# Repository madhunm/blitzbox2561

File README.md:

# blitzbox2561
mini-sized ECU for speeduino firmware (5x5 cm)

2 injectors<br/>
2 active ignition coils or 1 passive ignition coil with separate ground plane<br/>
1 crankshaft sensor with VR-conditioner<br/>
6 analog inputs: CLT, IAT, TPS, BAT, Wideband Lambda, onboard MAP (4250 or 6400)<br/>

1 fuel pump out<br/>

1 idle valve out<br/>
1 tacho out<br/>
4 free and non-wired general purpose I/O's<br/>
USB programming interface with PL2303SA (Tunerstudio)<br/>

all in/outputs can be programmed different

[Link to the original speeduino project](https://www.speeduino.com "speeduino homepage")

<p align="center">
  
  <br/>

</p>

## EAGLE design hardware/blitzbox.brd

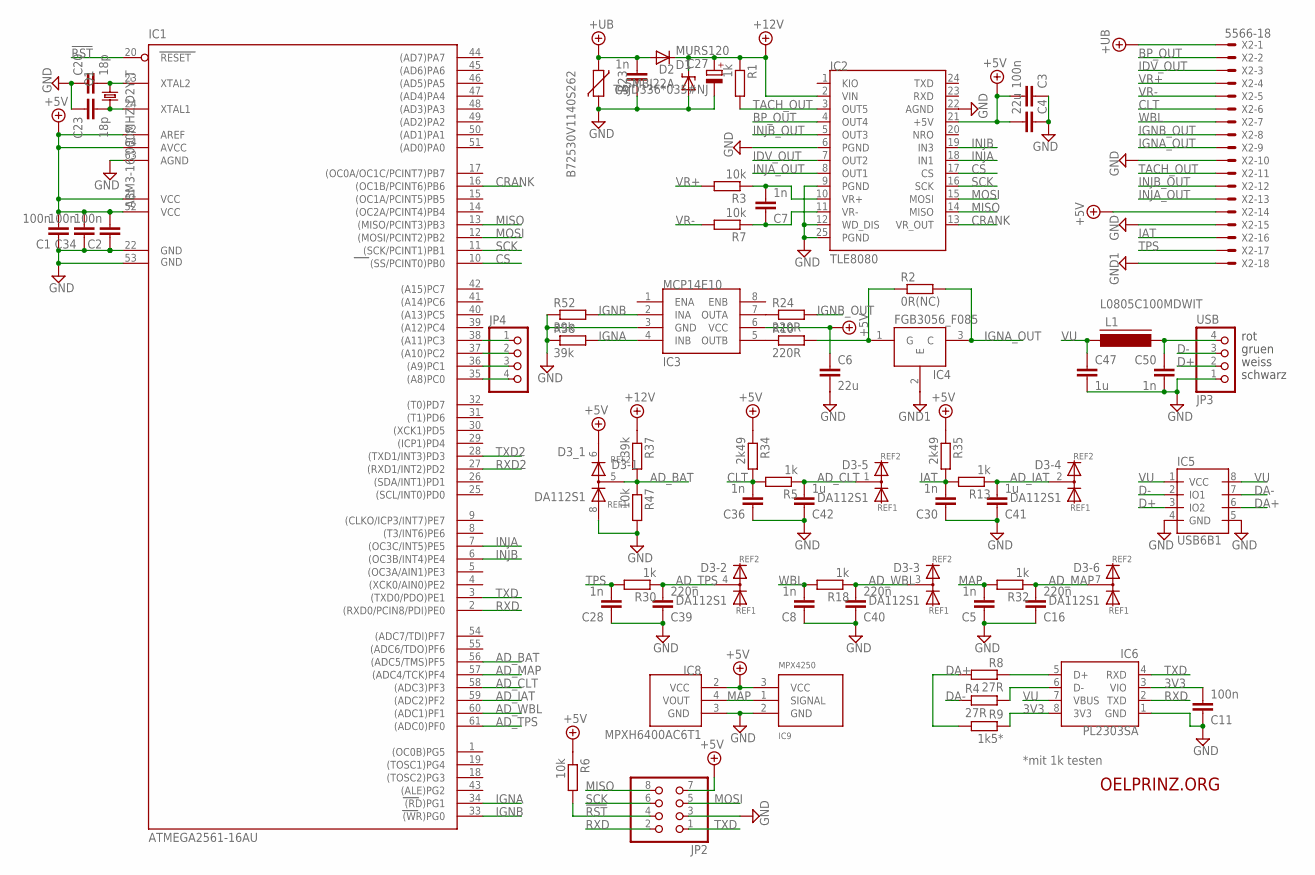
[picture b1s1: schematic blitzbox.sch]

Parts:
C1, C2, C3, C11, C34: 100n; C0805
C4: 22u; C1210
C5, C7, C8, C9, C28, C30, C36, C50: 1n; C0805
C6: 22u; C1206
C16, C39, C40: 220n; C0805
C20, C23: 18p; C0805
C27: TAJD336*035#NJ; SMC_D
C41, C42, C47: 1u; C0805
D1: MURS120
D2: SMBJ22A; SMBJ
D3: DA112S1; SO08
IC1: ATMEGA2561-16AU; TQFP64
IC2: TLE8080
IC3: MCP14E10; SO-08
IC4: FGB3056_F085; TO263
IC5: USB6B1; SO08
IC6: PL2303SA; SO-08
IC8: MPXH6400AC6T1; MPXH6400
IC9: MPX4250
JP2: PINHD-2X4; 2X04
JP3: USB; 1X04
JP4: PINHD-1X4; 1X04
L1: L0805C100MDWIT; FB805
Q1: ABM3-16.000MHZ-D2Y-T; ABM3
R1, R5, R13, R18, R30, R32: 1k; R0805
R2: 0R(NC); R0805
R3, R6, R7, R47: 10k; R0805
R4, R8: 27R; R0805
R9: 1k5*; R0805
R10, R24: 220R; R0805
R23: B72530V1140S262; CT/CN1210
R34, R35: 2k49; R0805
R37, R52, R58: 39k; R0805
X2: 5566-18

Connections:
3V3: C11.2, IC6.3 (VIO), IC6.8 (3V3), R9.1
!RST: IC1.20 (RESET), JP2.4, R6.2
+5V: C1.2, C2.2, C3.2, C4.2, C6.1, C34.2, D3.6 (REF2), IC1.21 (VCC), IC1.52 (VCC1), IC1.62 (AREF), IC1.64 (AVCC), IC2.21 (+5V), IC3.6 (VCC), IC8.2 (VCC), IC9.3 (VCC), JP2.7, R6.1, R34.1, R35.1, X2.14
+5VU: C50.1, JP3.4, L1.2
+12V: C27.+, D1.2 (C), D2.C, IC2.2 (VIN), R1.1, R37.1
+UB: C9.2, D1.1 (A), R23.2, X2.1
AD_BAT: D3.5 (K), IC1.56 ((ADC5/TMS)PF5), R37.2, R47.1
AD_CLT: C42.2, D3.1 (K), IC1.58 ((ADC3)PF3), R5.1
AD_IAT: C41.2, D3.2 (K), IC1.59 ((ADC2)PF2), R13.1
AD_MAP: C16.2, D3.7 (K), IC1.57 ((ADC4/TCK)PF4), R32.1
AD_TPS: C39.2, D3.4 (K), IC1.61 ((ADC0)PF0), R30.1
AD_WBL: C40.2, D3.3 (K), IC1.60 ((ADC1)PF1), R18.1
BP_OUT: IC2.4 (OUT4), X2.2
CLT: C36.2, R5.2, R34.2, X2.6
CRANK: IC1.16 ((OC1B/PCINT6)PB6), IC2.13 (VR_OUT)
CS: IC1.10 ((SS/PCINT0)PB0), IC2.17 (CS)
D+: IC5.3 (IO2), JP3.2
D-: IC5.2 (IO1), JP3.3
DA+: IC5.6 (IO2), R8.2, R9.2
DA-: IC5.7 (IO1), R4.1
GND: C1.1, C2.1, C3.1, C4.1, C5.1, C6.2, C8.1, C9.1, C11.1, C16.1, C20.1, C23.1, C27.-, C28.1, C30.1, C34.1, C36.1, C39.1, C40.1, C41.1, C42.1, C47.2, C50.2, D2.A, D3.8 (REF1), IC1.22 (GND), IC1.53 (GND1), IC1.63 (AGND), IC2.6 (PGND), IC2.9 (PGND), IC2.12 (WD_DIS), IC2.22 (AGND), IC2.25 (PGND), IC3.3 (GND), IC5.4 (GND), IC5.5 (GND), IC6.1 (GND), IC8.3 (GND), IC9.2 (GND), JP2.3, JP3.1, R23.1, R47.2, R52.1, R58.1, X2.10, X2.15
GND1: IC4.2 (E), X2.18
IAT: C30.2, R13.2, R35.2, X2.16
IDV_OUT: IC2.7 (OUT2), X2.3
IGN: IC4.1 (G), R2.1, R10.2
IGNA: IC1.34 ((RD)PG1), IC3.4 (INB), R58.2
IGNA_OUT: IC4.3 (C), R2.2, X2.9
IGNB: IC1.33 ((WR)PG0), IC3.2 (INA), R52.2
IGNB_OUT: R24.2, X2.8
INJA: IC1.7 ((OC3C/INT5)PE5), IC2.18 (IN1)
INJA_OUT: IC2.8 (OUT1), X2.13
INJB: IC1.6 ((OC3B/INT4)PE4), IC2.19 (IN3)
INJB_OUT: IC2.5 (OUT3), X2.12
MAP: C5.2, IC8.4 (VOUT), IC9.1 (SIGNAL), R32.2
MISO: IC1.13 ((MISO/PCINT3)PB3), IC2.14 (MISO), JP2.8
MOSI: IC1.12 ((MOSI/PCINT2)PB2), IC2.15 (MOSI), JP2.5
unnamed: C7.1, IC2.11 (VR-), R7.1
unnamed: IC3.5 (OUTB), R10.1
unnamed: IC6.6 (D-), R4.2
unnamed: IC6.5 (D+), R8.1
unnamed: IC1.38 ((A11)PC3), JP4.1
unnamed: IC1.37 ((A10)PC2), JP4.2
unnamed: IC1.36 ((A9)PC1), JP4.3
unnamed: IC1.35 ((A8)PC0), JP4.4
unnamed: C7.2, IC2.10 (VR+), R3.1
unnamed: IC3.7 (OUTA), R24.1
RXD: IC1.2 ((RXD0/PCIN8/PDI)PE0), IC6.2 (TXD), JP2.2
RXD2: IC1.27 ((RXD1/INT2)PD2)
SCK: IC1.11 ((SCK/PCINT1)PB1), IC2.16 (SCK), JP2.6
TACH_OUT: IC2.3 (OUT5), R1.2, X2.11
TPS: C28.2, R30.2, X2.17
TXD: IC1.3 ((TXD0/PDO)PE1), IC6.4 (RXD), JP2.1
TXD2: IC1.28 ((TXD1/INT3)PD3)
VR+: R3.2, X2.4
VR-: R7.2, X2.5
VU: C47.1, IC5.1 (VCC), IC5.8 (VCC), IC6.7 (VBUS), L1.1
WBL: C8.2, R18.2, X2.7
XTAL1: C20.2, IC1.23 (XTAL2), Q1.1
XTAL2: C23.2, IC1.24 (XTAL1), Q1.2

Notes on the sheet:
rot
gruen
weiss
schwarz
OELPRINZ.ORG
*mit 1k testen

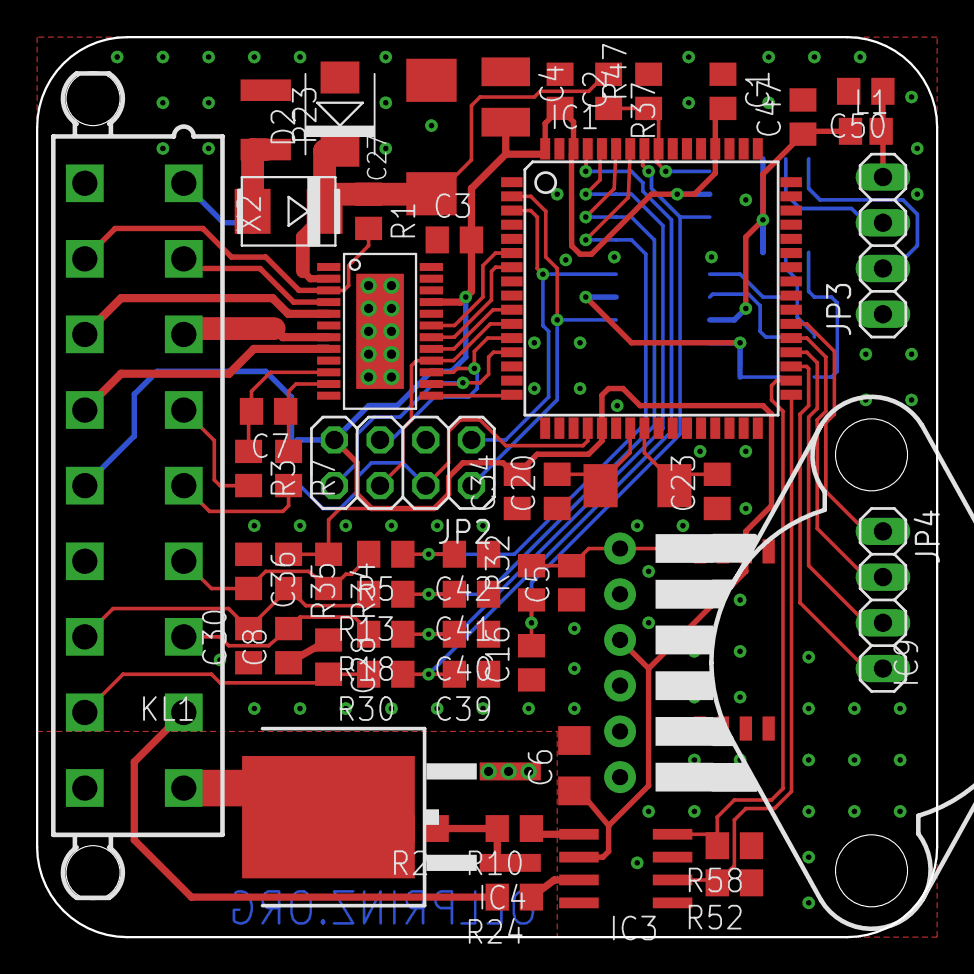
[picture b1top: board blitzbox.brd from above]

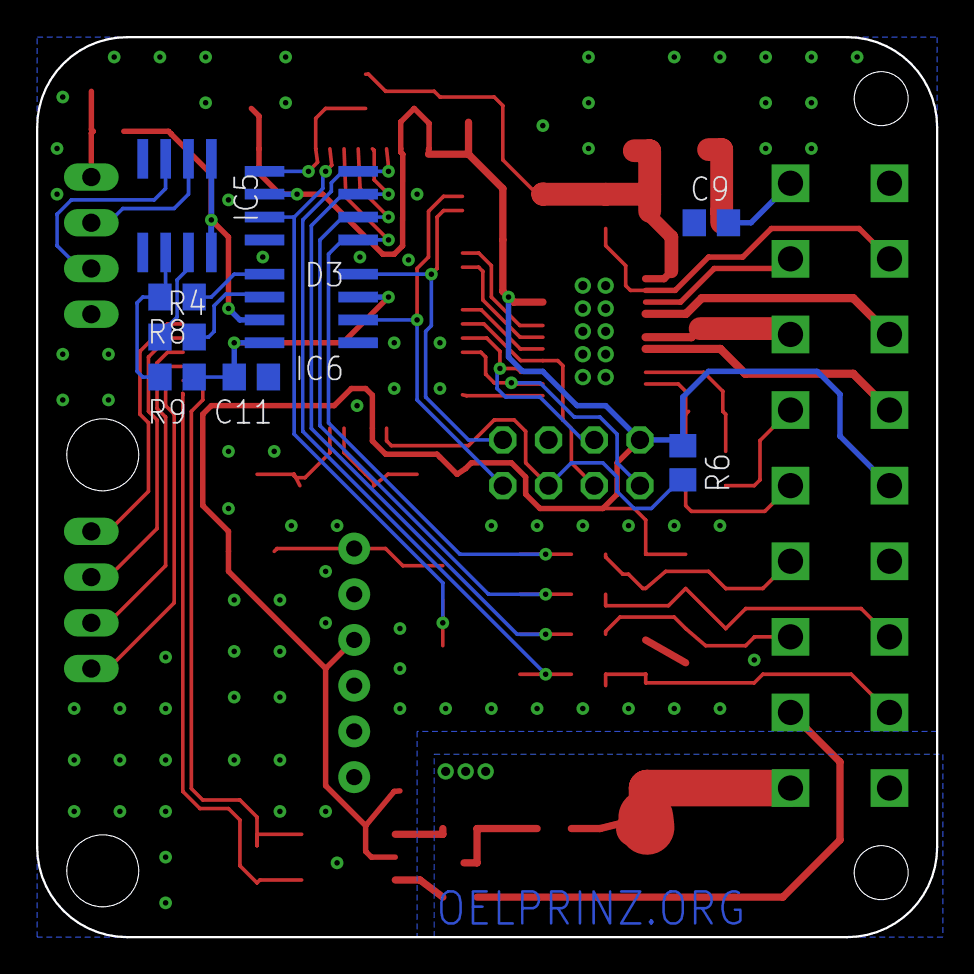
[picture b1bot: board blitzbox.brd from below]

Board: 2 copper layers, 50.0 x 50.0 mm, 63 parts (9 on the bottom side), 57 nets.

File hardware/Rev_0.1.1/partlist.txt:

Partlist

Exported from blitzbox.brd at 27.08.19 10:24

EAGLE Version 8.2.0 Copyright (c) 1988-2017 Autodesk, Inc.

Assembly variant: 

Part     Value                Package   Library             Position (mil)        Orientation

C1       100n                 C0805     rcl                 (1500 1850)           R270
C2       100n                 C0805     rcl                 (1143.75 1850)        R270
C3       100n                 C0805     rcl                 (912.5 1525)          R0
C4       22u                  C1210     rcl                 (1025 1825)           R270
C5       1n                   C0805     rcl                 (1168.75 775)         R90
C6       22u                  C1206     rcl                 (1175 375)            R90
C7       1n                   C0805     rcl                 (506.25 1150)         R180
C8       1n                   C0805     rcl                 (550 637.5)           R90
C9       1n                   C0805     rcl                 (493.75 1562.5)       MR0
C11      100n                 C0805     rcl                 (1500 1225)           MR180
C16      220n                 C0805     rcl                 (1081.25 600)         R90
C20      18p                  C0805     rcl                 (1137.5 975)          R90
C23      18p                  C0805     rcl                 (1487.5 975)          R90
C27      TAJD336*035#NJ       SMC_D     rcl                 (862.5 1750)          R90
C28      1n                   C0805     rcl                 (637.5 612.5)         R270
C30      1n                   C0805     rcl                 (462.5 637.5)         R90
C34      100n                 C0805     rcl                 (1050 975)            R90
C36      1n                   C0805     rcl                 (462.5 800)           R270
C39      220n                 C0805     rcl                 (950 575)             R180
C40      220n                 C0805     rcl                 (950 662.5)           R180
C41      1u                   C0805     rcl                 (950 750)             R180
C42      1u                   C0805     rcl                 (950 837.5)           R180
C47      1u                   C0805     rcl                 (1550 1800)           MR0
C50      1n                   C0805     rcl                 (1812.5 1850)         R180
D1       MURS120              MURS120   murs120             (550 1587.5)          R0
D2       SMBJ22A              SMBJ      diode               (662.5 1800)          R90
D3       DA112S1              SO08      st-microelectronics (1368.75 1600)        MR90
IC1      ATMEGA2561-16AU      TQFP64    atmel-2005          (1343.75 1418.75)     R0
IC2      TLE8080              TLE8080   tle8080             (750 1325)            R270
IC3      MCP14E10             SO-08     mcp14e10            (1287.5 150)          R90
IC4      FGB3056_F085         TO263     FGB3056_F085        (775 262.5)           R90
IC5      USB6B1               SO08      st-microelectronics (1662.5 1600)         MR180
IC6      PL2303SA             SO-08     PL2303SA            (1368.75 1375)        MR90
IC8      MPXH6400AC6T1        MPXH6400  MPXH6400            (1525 650)            R270
IC9      MPX4250              MPX4250   mpx4250             (1825 600)            R270
JP2                           2X04      pinhead             (800 1037.5)          R180
JP3      USB                  1X04      pinhead             (1850 1512.5)         R90
JP4                           1X04      pinhead             (1850 737.5)          R270
L1       L0805C100MDWIT       FB805     dp_devices          (1812.5 1762.5)       R0
Q1       ABM3-16.000MHZ-D2Y-T ABM3      ABM3                (1313.1282 987.42384) R0
R1       1k                   R0805     rcl                 (725 1587.5)          R270
R2       0R(NC)               R0805     rcl                 (837.5 237.5)         R180
R3       10k                  R0805     rcl                 (462.5 1025)          R270
R4       27R                  R0805     rcl                 (1662.5 1312.5)       MR0
R5       1k                   R0805     rcl                 (762.5 837.5)         R180
R6       10k                  R0805     rcl                 (556.25 1037.5)       MR270
R7       10k                  R0805     rcl                 (550 1025)            R270
R8       27R                  R0805     rcl                 (1662.5 1400)         MR180
R9       1k5*                 R0805     rcl                 (1662.5 1225)         MR180
R10      220R                 R0805     rcl                 (1043.75 237.5)       R180
R13      1k                   R0805     rcl                 (762.5 750)           R180
R18      1k                   R0805     rcl                 (762.5 662.5)         R180
R23      B72530V1140S262      CT/CN1210 varistor            (500 1787.5)          R270
R24      220R                 R0805     rcl                 (1043.75 87.5)        R180
R30      1k                   R0805     rcl                 (762.5 575)           R180
R32      1k                   R0805     rcl                 (1081.25 775)         R90
R34      2k49                 R0805     rcl                 (637.5 800)           R270
R35      2k49                 R0805     rcl                 (550 800)             R270
R37      39k                  R0805     rcl                 (1250 1850)           R270
R47      10k                  R0805     rcl                 (1337.5 1850)         R90
R52      39k                  R0805     rcl                 (1525 118.75)         R180
R58      39k                  R0805     rcl                 (1525 200)            R180
X2       5566-18              5566-18   con-molex           (212.5 987.5)         R90

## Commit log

2019-08-21 Create *
